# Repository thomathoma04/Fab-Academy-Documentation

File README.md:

# Tom - Fab Academy

## Getting started

To make it easy for you to get started with GitLab, here's a list of recommended next steps.

Already a pro? Just edit this README.md and make it your own. Want to make it easy? [Use the template at the bottom](#editing-this-readme)!

## Add your files

- [ ] [Create](https://docs.gitlab.com/ee/user/project/repository/web_editor.html#create-a-file) or [upload](https://docs.gitlab.com/ee/user/project/repository/web_editor.html#upload-a-file) files
- [ ] [Add files using the command line](https://docs.gitlab.com/ee/gitlab-basics/add-file.html#add-a-file-using-the-command-line) or push an existing Git repository with the following command:

```
cd existing_repo
git remote add origin https://git.fablabkerala.in/tom/tom-fab-academy.git
git branch -M main
git push -uf origin main
```

## Integrate with your tools

- [ ] [Set up project integrations](https://git.fablabkerala.in/tom/tom-fab-academy/-/settings/integrations)

## Collaborate with your team

- [ ] [Invite team members and collaborators](https://docs.gitlab.com/ee/user/project/members/)
- [ ] [Create a new merge request](https://docs.gitlab.com/ee/user/project/merge_requests/creating_merge_requests.html)
- [ ] [Automatically close issues from merge requests](https://docs.gitlab.com/ee/user/project/issues/managing_issues.html#closing-issues-automatically)
- [ ] [Enable merge request approvals](https://docs.gitlab.com/ee/user/project/merge_requests/approvals/)
- [ ] [Automatically merge when pipeline succeeds](https://docs.gitlab.com/ee/user/project/merge_requests/merge_when_pipeline_succeeds.html)

## Test and Deploy

Use the built-in continuous integration in GitLab.

- [ ] [Get started with GitLab CI/CD](https://docs.gitlab.com/ee/ci/quick_start/index.html)
- [ ] [Analyze your code for known vulnerabilities with Static Application Security Testing(SAST)](https://docs.gitlab.com/ee/user/application_security/sast/)
- [ ] [Deploy to Kubernetes, Amazon EC2, or Amazon ECS using Auto Deploy](https://docs.gitlab.com/ee/topics/autodevops/requirements.html)
- [ ] [Use pull-based deployments for improved Kubernetes management](https://docs.gitlab.com/ee/user/clusters/agent/)
- [ ] [Set up protected environments](https://docs.gitlab.com/ee/ci/environments/protected_environments.html)

***

# Editing this README

When you're ready to make this README your own, just edit this file and use the handy template below (or feel free to structure it however you want - this is just a starting point!).  Thank you to [makeareadme.com](https://www.makeareadme.com/) for this template.

## Suggestions for a good README
Every project is different, so consider which of these sections apply to yours. The sections used in the template are suggestions for most open source projects. Also keep in mind that while a README can be too long and detailed, too long is better than too short. If you think your README is too long, consider utilizing another form of documentation rather than cutting out information.

## Name
Choose a self-explaining name for your project.

## Description
Let people know what your project can do specifically. Provide context and add a link to any reference visitors might be unfamiliar with. A list of Features or a Background subsection can also be added here. If there are alternatives to your project, this is a good place to list differentiating factors.

## Badges
On some READMEs, you may see small images that convey metadata, such as whether or not all the tests are passing for the project. You can use Shields to add some to your README. Many services also have instructions for adding a badge.

## Visuals
Depending on what you are making, it can be a good idea to include screenshots or even a video (you'll frequently see GIFs rather than actual videos). Tools like ttygif can help, but check out Asciinema for a more sophisticated method.

## Installation
Within a particular ecosystem, there may be a common way of installing things, such as using Yarn, NuGet, or Homebrew. However, consider the possibility that whoever is reading your README is a novice and would like more guidance. Listing specific steps helps remove ambiguity and gets people to using your project as quickly as possible. If it only runs in a specific context like a particular programming language version or operating system or has dependencies that have to be installed manually, also add a Requirements subsection.

## Usage
Use examples liberally, and show the expected output if you can. It's helpful to have inline the smallest example of usage that you can demonstrate, while providing links to more sophisticated examples if they are too long to reasonably include in the README.

## Support
Tell people where they can go to for help. It can be any combination of an issue tracker, a chat room, an email address, etc.

## Roadmap
If you have ideas for releases in the future, it is a good idea to list them in the README.

## Contributing
State if you are open to contributions and what your requirements are for accepting them.

For people who want to make changes to your project, it's helpful to have some documentation on how to get started. Perhaps there is a script that they should run or some environment variables that they need to set. Make these steps explicit. These instructions could also be useful to your future self.

You can also document commands to lint the code or run tests. These steps help to ensure high code quality and reduce the likelihood that the changes inadvertently break something. Having instructions for running tests is especially helpful if it requires external setup, such as starting a Selenium server for testing in a browser.

## Authors and acknowledgment
Show your appreciation to those who have contributed to the project.

## License
For open source projects, say how it is licensed.

## Project status
If you have run out of energy or time for your project, put a note at the top of the README saying that development has slowed down or stopped completely. Someone may choose to fork your project or volunteer to step in as a maintainer or owner, allowing your project to keep going. You can also make an explicit request for maintainers.

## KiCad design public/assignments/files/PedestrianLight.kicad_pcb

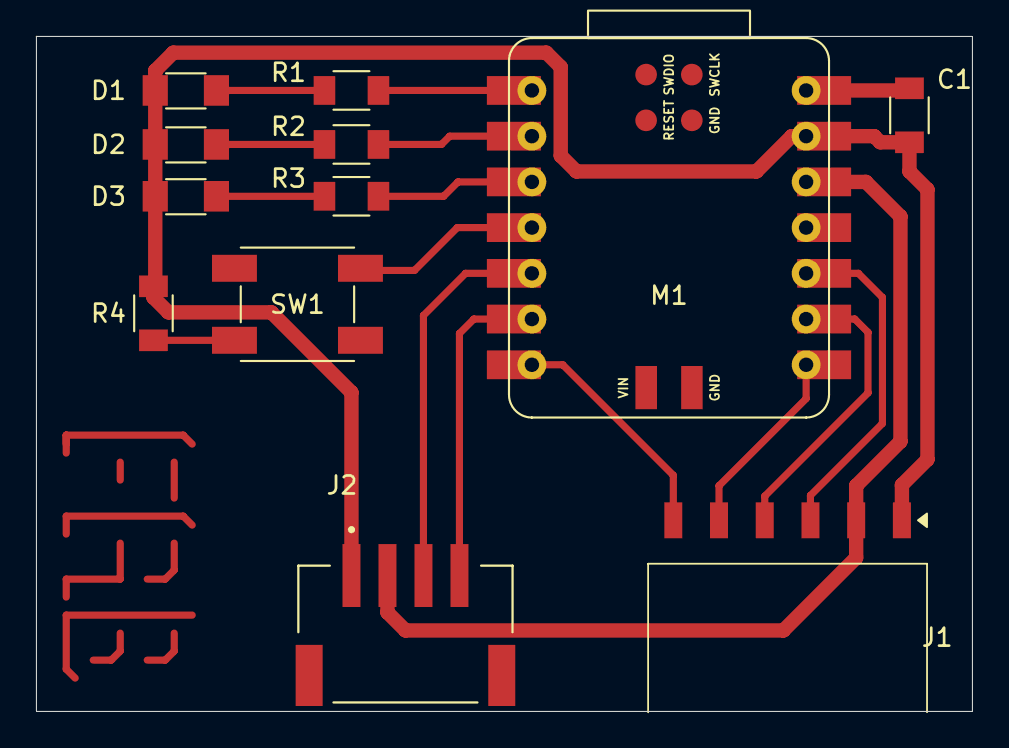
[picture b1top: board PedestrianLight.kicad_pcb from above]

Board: 2 copper layers, 52.0 x 37.5 mm, 12 parts (0 on the bottom side), 17 nets.

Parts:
C1: C_1206
D1, D2, D3: LED_1206
J1: PinSocket_01x06_P2.54mm_Horizontal_SMD
J2: S4B-PH-SM4-TB; JST_S4B-PH-SM4-TB
M1: Module_XIAO-RP2040; SeeedStudio_XIAO_RP2040
R1, R2, R3, R4: R_1206
SW1: Switch_Tactile_Omron; Button_Omron_B3SN_6.0x6.0mm

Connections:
Button: M1.4 (D3), SW1.2
D6: J1.6, M1.7 (D6)
D7: J1.5, M1.8 (D7)
D8: J1.4, M1.9 (D8)
D9: J1.3, M1.10 (D9)
LED1: M1.1 (D0), R1.2
LED2: M1.2 (D1), R2.2
LED3: M1.3 (D2), R3.2
unnamed: D1.2 (A), R1.1
unnamed: D2.2 (A), R2.1
unnamed: D3.2 (A), R3.1
unnamed: R4.2, SW1.1
PWR_3V3: J1.2, J2.2, M1.12 (3V3)
PWR_5V: C1.1, M1.14 (5V)
PWR_GND: C1.2, D1.1 (K), D2.1 (K), D3.1 (K), J1.1, J2.1, M1.13 (GND), R4.1
SCL: J2.4, M1.6 (D5)
SDA: J2.3, M1.5 (D4)

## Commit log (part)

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2026-06-06 Moved from FabLAb Repo to personal repo
